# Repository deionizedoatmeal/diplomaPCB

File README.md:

### Bill of Materials:
Parts for the board:
| Part           | Quantity | Package          | Value          | Link                      |
| -------------- |:--------:|:----------------:|:--------------:|:-------------------------:|
| Microprocessor | 1        | QFN-56           | RP2040         |                           |
| 8MB SPI Flash  | 1        | SOIC-8           |                |                           |
| NeoPixel LED   | 37       | 1515 LED         | SK6805-E-J     | [Adafruit](https://www.adafruit.com/product/4492) |
| 7 Segement LED | 4        | LTS6760          | Common Cathode |                           | 
| Button Switch  | 5        | KMR2             | Momentary      |                           |
| Schottky Diode | 4        | SOD-123          | MBR0540        |                           |
| Transistor     | 14       | SOT-23           |                |                           |
| Crystal        | 1        | 2.5mm X 2.0mm    | 12.000 MHz     |                           |
| I2C Quad ADC   | 8        | SOIC-16          | PCF8591        |                           |
| Quad Logic Shifter | 1    | SOIC-16          | 74AHCT125      |                           |
| Voltage Regulator | 4     | SOT-23-5         | AP2112K-3.3    |                           |
| USB-C Receptacle | 5      | SMD              |                |                           |
| USB-C Plug     | 4        | SMD Edge Launch  | | [Adafruit](https://www.adafruit.com/product/4932) [Digikey](https://www.digikey.com/en/products/detail/adafruit-industries-llc/4932/13997774) |
| Resistor       | 23       | 0603/1608 Metric | 300 Ω          |                           |
| Resistor       | 10       | 0603/1608 Metric | 1 kΩ           |                           |
| Resistor       | 2        | 0603/1608 Metric | 5.11 kΩ        |                           |
| Resistor       | 60       | 0603/1608 Metric | 10 kΩ          |                           |
| Resistor       | 9        | 0603/1608 Metric | 1 MΩ           |                           |
| Resistor       | 2        | 0402/1005 Metric | 27 Ω           |                           |
| Capacitor      | 45       | 0805/2012 Metric | 0.1 µF         |                           |
| Capacitor      | 20       | 0085/2012 Metric | 10 µF          |                           |
| Capacitor      | 2        | 0402/1005 Metric | 27 pF          |                           |
| Capacitor      | 10       | 0402/1005 Metric | 100 nF         |                           |
| Capacitor      | 2        | 0402/1005 Metric | 1 µF           |                           |
| Magnets        | 112      | 3mm diameter x 1mm | Neodymium    |                           |

Parts for the game pieces (assuming 20 pieces for each nationality):
| Part           | Quantity | Package          | Value          | Link                      |
| -------------- |:--------:|:----------------:|:--------------:|:-------------------------:|
| Resistor       | 20       | Through Hole     | 60 kΩ          |                           |
| Resistor       | 20       | Through Hole     | 25 kΩ          |                           |
| Resistor       | 20       | Through Hole     | 13.4 kΩ        |                           |
| Resistor       | 20       | Through Hole     | 7.5 kΩ         |                           |
| Resistor       | 20       | Through Hole     | 4 kΩ           |                           |
| Resistor       | 20       | Through Hole     | 1.7 kΩ         |                           |
| Resistor       | 20       | Through Hole     | 0 Ω            |                           |
| Magnets        | 140      | 3mm diameter x 1mm | Neodymium    |                           |
| Pogo Pins      | 140      | anything that makes good contact with 2mm diameter pads and fits inside the piece | | [Digikey](https://www.digikey.com/en/products/detail/mill-max-manufacturing-corp/0965-0-15-20-80-14-11-0/2784013) |

### 3D Printing Pieces:

### Assembly Instructions:

### Software Install Instructions:
1) Hold down boot button on underside while plugging USB into computer.
2) When the `RPI-RP2` device shows up, copy [Adafruit's CircuitPython library](https://circuitpython.org/board/adafruit_feather_rp2040/) to the volume. 
3) Wait for the device to disappear and reappear as `CURCUITPY`, then copy all the libraries into the `lib` directory on the RP2040.
4) Finally, copy `code.py` into the `CURCUITPY` volume.

### Images

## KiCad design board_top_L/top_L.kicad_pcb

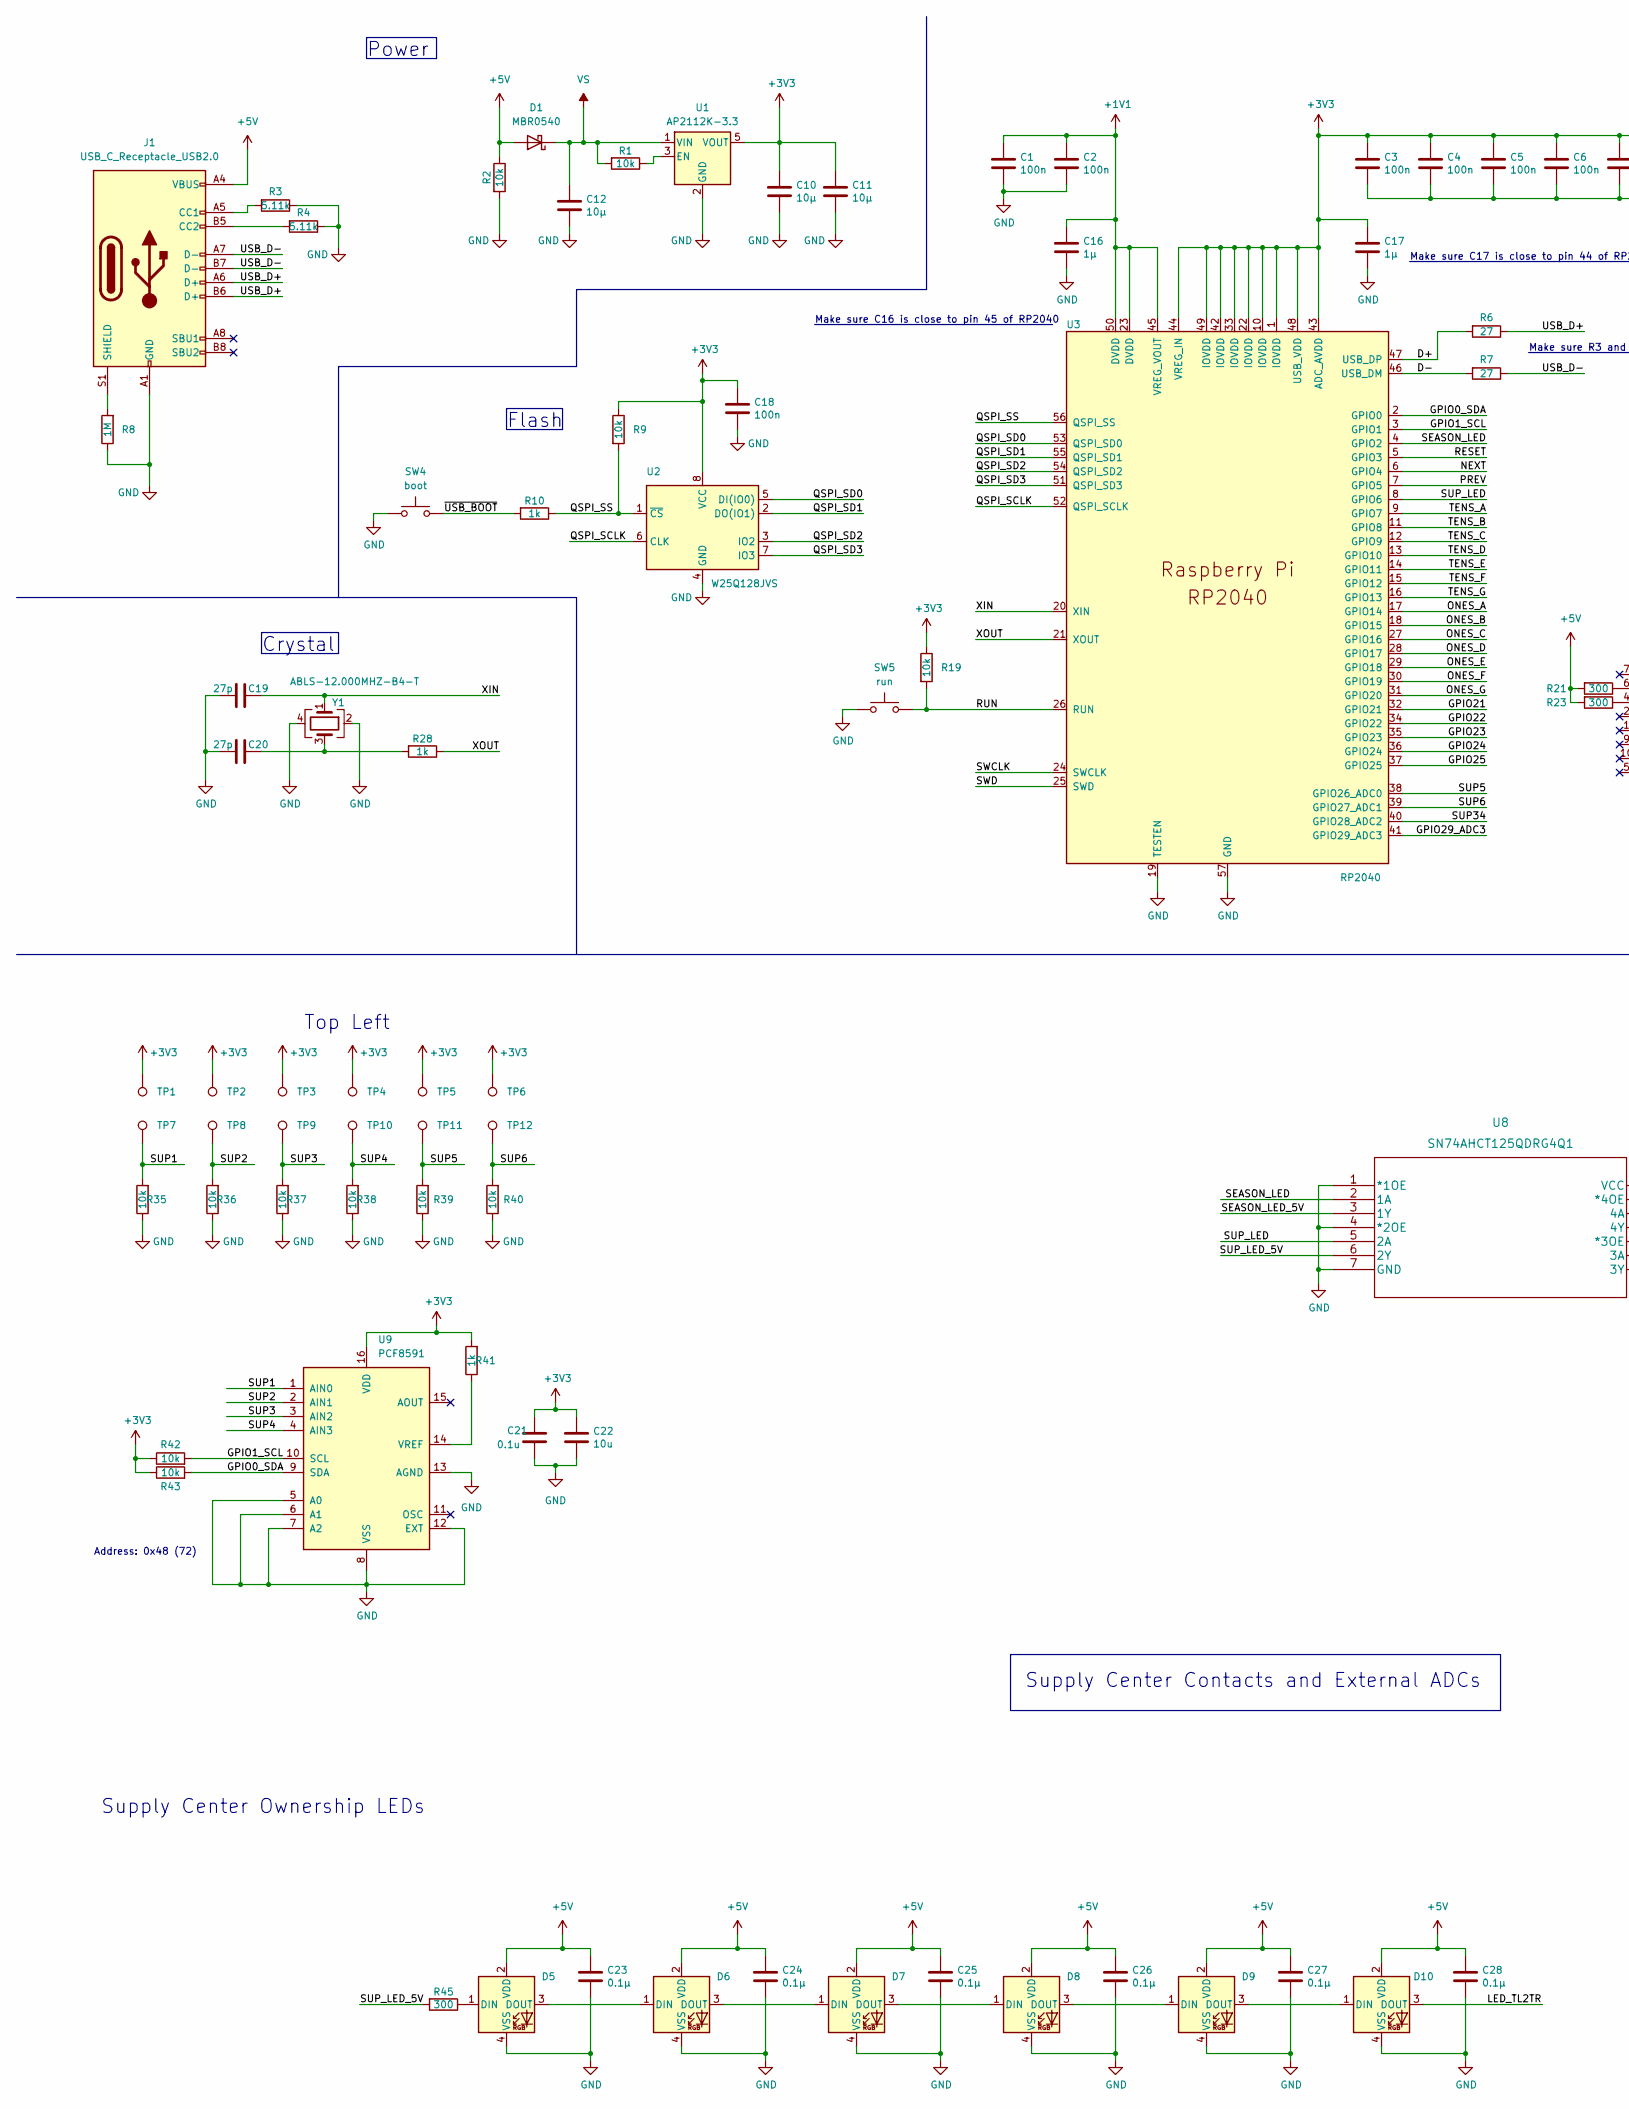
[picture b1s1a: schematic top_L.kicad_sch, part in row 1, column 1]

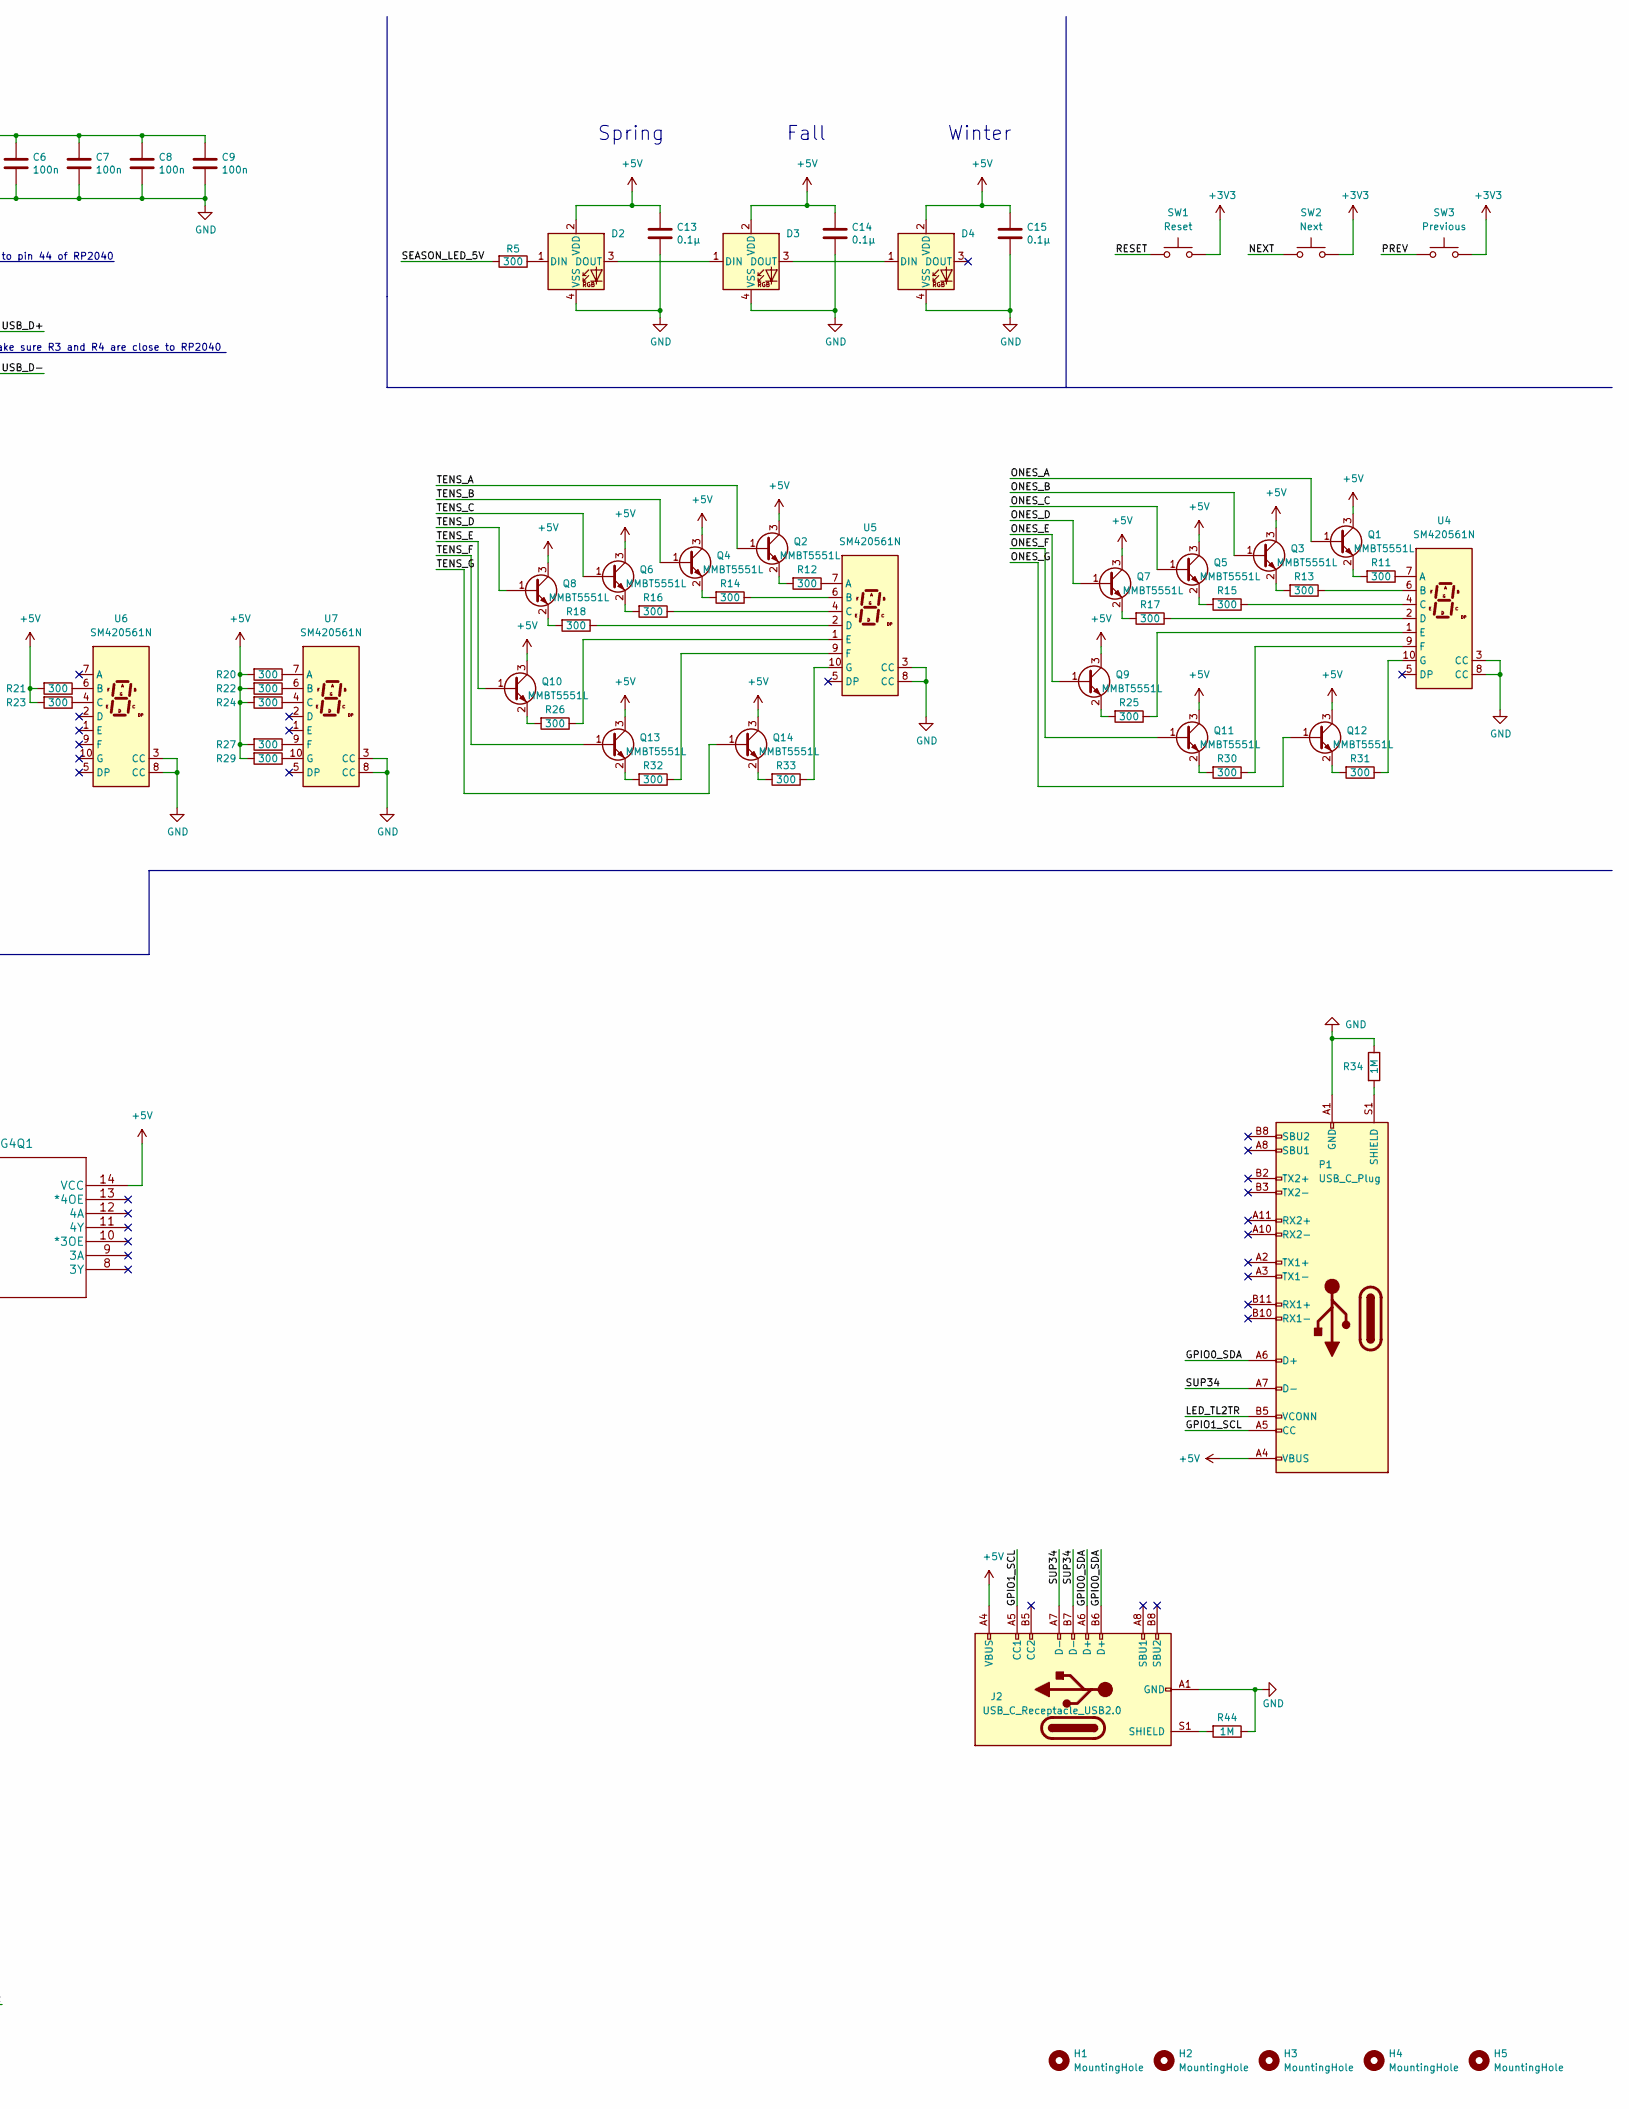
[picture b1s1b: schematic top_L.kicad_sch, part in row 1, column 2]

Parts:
C1, C2, C3, C4, C5, C6, C7, C8, C9, C18: 100n; C_0402_1005Metric
C10, C11, C12: 10µ; C_0805_2012Metric
C13, C14, C15, C23, C24, C25, C26, C27, C28: 0.1µ; C_0805_2012Metric
C16, C17: 1µ; C_0402_1005Metric
C19, C20: 27p; C_0402_1005Metric
C21: 0.1u; C_0805_2012Metric
C22: 10u; C_0805_2012Metric
D1: MBR0540; D_SOD-123
D2, D3, D4, D5, D6, D7, D8, D9, D10: SK6805-EC
H1, H2, H3, H4, H5: MountingHole; MountingHole_2.2mm_M2
J1, J2: USB_C_Receptacle_USB2.0; USB_C_Receptacle_HRO_TYPE-C-31-M-12
P1: USB_C_Plug; USB_C_Plug_edge_launch
Q1, Q2, Q3, Q4, Q5, Q6, Q7, Q8, Q9, Q10, Q11, Q12, Q13, Q14: MMBT5551L; SOT-23
R1, R2, R9, R19, R35, R36, R37, R38, R39, R40, R42, R43: 10k; R_0603_1608Metric
R3, R4: 5.11k; R_0603_1608Metric
R5, R11, R12, R13, R14, R15, R16, R17, R18, R20, R21, R22, R23, R24, R25, R26, R27, R29, R30, R31, R32, R33, R45: 300; R_0603_1608Metric
R6, R7: 27; R_0402_1005Metric
R8, R34, R44: 1M; R_0603_1608Metric
R10, R28, R41: 1k; R_0603_1608Metric
SW1: Reset; SW_Push_1P1T_NO_CK_KMR2
SW2: Next; SW_Push_1P1T_NO_CK_KMR2
SW3: Previous; SW_Push_1P1T_NO_CK_KMR2
SW4: boot; SW_Push_1P1T_NO_CK_KMR2
SW5: run; SW_Push_1P1T_NO_CK_KMR2
TP1, TP2, TP3, TP4, TP5, TP6, TP7, TP8, TP9, TP10, TP11, TP12: TestPoint; TestPoint_Pad_D2.0mm
U1: AP2112K-3.3; SOT-23-5
U2: W25Q128JVS; SOIC-8_5.23x5.23mm_P1.27mm
U3: RP2040; RP2040-QFN-56
U4, U5, U6, U7: SM420561N; 7SegmentLED_LTS6760_LTS6780
U8: SN74AHCT125QDRG4Q1
U9: PCF8591; SOIC-16W_7.5x10.3mm_P1.27mm
Y1: ABLS-12.000MHZ-B4-T; Crystal_SMD_3225-4Pin_3.2x2.5mm

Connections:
+1V1: C1.1, C2.1, C16.1, U3.23 (DVDD), U3.45 (VREG_VOUT), U3.50 (DVDD)
+3V3: C3.1, C4.1, C5.1, C6.1, C7.1, C8.1, C9.1, C10.1, C11.1, C17.1, C18.1, C21.1, C22.1, R9.1, R19.1, R41.2, R42.1, R43.1, SW1.2, SW2.2, SW3.2, TP1.1, TP2.1, TP3.1, TP4.1, TP5.1, TP6.1, U1.5 (VOUT), U2.8 (VCC), U3.1 (IOVDD), U3.10 (IOVDD), U3.22 (IOVDD), U3.33 (IOVDD), U3.42 (IOVDD), U3.43 (ADC_AVDD), U3.44 (VREG_IN), U3.48 (USB_VDD), U3.49 (IOVDD), U9.16 (VDD)
+5V: C13.1, C14.1, C15.1, C23.1, C24.1, C25.1, C26.1, C27.1, C28.1, D1.2 (A), D2.2 (VDD), D3.2 (VDD), D4.2 (VDD), D5.2 (VDD), D6.2 (VDD), D7.2 (VDD), D8.2 (VDD), D9.2 (VDD), D10.2 (VDD), J1.A4 (VBUS), J1.A9 (VBUS), J1.B4 (VBUS), J1.B9 (VBUS), J2.A4 (VBUS), J2.A9 (VBUS), J2.B4 (VBUS), J2.B9 (VBUS), P1.A4 (VBUS), P1.A9 (VBUS), P1.B4 (VBUS), P1.B9 (VBUS), Q1.3 (C), Q2.3 (C), Q3.3 (C), Q4.3 (C), Q5.3 (C), Q6.3 (C), Q7.3 (C), Q8.3 (C), Q9.3 (C), Q10.3 (C), Q11.3 (C), Q12.3 (C), Q13.3 (C), Q14.3 (C), R2.1, R20.2, R21.2, R22.2, R23.2, R24.2, R27.2, R29.2, U8.14 (VCC)
/D+: R6.2, U3.47 (USB_DP)
/D-: R7.2, U3.46 (USB_DM)
/GPIO0_SDA: J2.A6 (D+), J2.B6 (D+), P1.A6 (D+), R43.2, U3.2 (GPIO0), U9.9 (SDA)
/GPIO1_SCL: J2.A5 (CC1), P1.A5 (CC), R42.2, U3.3 (GPIO1), U9.10 (SCL)
/GPIO21: U3.32 (GPIO21)
/GPIO22: U3.34 (GPIO22)
/GPIO23: U3.35 (GPIO23)
/GPIO24: U3.36 (GPIO24)
/GPIO25: U3.37 (GPIO25)
/GPIO29_ADC3: U3.41 (GPIO29_ADC3)
/LED_TL2TR: D10.3 (DOUT), P1.B5 (VCONN)
/NEXT: SW2.1, U3.6 (GPIO4)
/ONES_A: Q1.1 (B), U3.17 (GPIO14)
/ONES_B: Q3.1 (B), U3.18 (GPIO15)
/ONES_C: Q5.1 (B), U3.27 (GPIO16)
/ONES_D: Q7.1 (B), U3.28 (GPIO17)
/ONES_E: Q9.1 (B), U3.29 (GPIO18)
/ONES_F: Q11.1 (B), U3.30 (GPIO19)
/ONES_G: Q12.1 (B), U3.31 (GPIO20)
/PREV: SW3.1, U3.7 (GPIO5)
/QSPI_SCLK: U2.6 (CLK), U3.52 (QSPI_SCLK)
/QSPI_SD0: U2.5 (DI(IO0)), U3.53 (QSPI_SD0)
/QSPI_SD1: U2.2 (DO(IO1)), U3.55 (QSPI_SD1)
/QSPI_SD2: U2.3 (IO2), U3.54 (QSPI_SD2)
/QSPI_SD3: U2.7 (IO3), U3.51 (QSPI_SD3)
/QSPI_SS: R9.2, R10.1, U2.1 (~CS), U3.56 (QSPI_SS)
/RESET: SW1.1, U3.5 (GPIO3)
/RUN: R19.2, SW5.2, U3.26 (RUN)
/SEASON_LED: U3.4 (GPIO2), U8.2 (1A)
/SEASON_LED_5V: R5.2, U8.3 (1Y)
/SUP1: R35.2, TP7.1, U9.1 (AIN0)
/SUP2: R36.2, TP8.1, U9.2 (AIN1)
/SUP3: R37.2, TP9.1, U9.3 (AIN2)
/SUP4: R38.2, TP10.1, U9.4 (AIN3)
/SUP5: R39.2, TP11.1, U3.38 (GPIO26_ADC0)
/SUP6: R40.2, TP12.1, U3.39 (GPIO27_ADC1)
/SUP34: J2.A7 (D-), J2.B7 (D-), P1.A7 (D-), U3.40 (GPIO28_ADC2)
/SUP_LED: U3.8 (GPIO6), U8.5 (2A)
/SUP_LED_5V: R45.2, U8.6 (2Y)
/SWCLK: U3.24 (SWCLK)
/SWD: U3.25 (SWD)
/TENS_A: Q2.1 (B), U3.9 (GPIO7)
/TENS_B: Q4.1 (B), U3.11 (GPIO8)
/TENS_C: Q6.1 (B), U3.12 (GPIO9)
/TENS_D: Q8.1 (B), U3.13 (GPIO10)
/TENS_E: Q10.1 (B), U3.14 (GPIO11)
/TENS_F: Q13.1 (B), U3.15 (GPIO12)
/TENS_G: Q14.1 (B), U3.16 (GPIO13)
/USB_D+: J1.A6 (D+), J1.B6 (D+), R6.1
/USB_D-: J1.A7 (D-), J1.B7 (D-), R7.1
/XIN: C19.1, U3.20 (XIN), Y1.1
/XOUT: R28.1, U3.21 (XOUT)
/~USB_BOOT: R10.2, SW4.2
GND: C1.2, C2.2, C3.2, C4.2, C5.2, C6.2, C7.2, C8.2, C9.2, C10.2, C11.2, C12.2, C13.2, C14.2, C15.2, C16.2, C17.2, C18.2, C19.2, C20.2, C21.2, C22.2, C23.2, C24.2, C25.2, C26.2, C27.2, C28.2, D2.4 (VSS), D3.4 (VSS), D4.4 (VSS), D5.4 (VSS), D6.4 (VSS), D7.4 (VSS), D8.4 (VSS), D9.4 (VSS), D10.4 (VSS), J1.A1 (GND), J1.A12 (GND), J1.B1 (GND), J1.B12 (GND), J2.A1 (GND), J2.A12 (GND), J2.B1 (GND), J2.B12 (GND), P1.A1 (GND), P1.A12 (GND), P1.B1 (GND), P1.B12 (GND), R2.2, R3.1, R4.1, R8.1, R34.1, R35.1, R36.1, R37.1, R38.1, R39.1, R40.1, R44.1, SW4.1, SW5.1, U1.2 (GND), U2.4 (GND), U3.19 (TESTEN), U3.57 (GND), U4.3 (CC), U4.8 (CC), U5.3 (CC), U5.8 (CC), U6.3 (CC), U6.8 (CC), U7.3 (CC), U7.8 (CC), U8.1 (*1OE), U8.4 (*2OE), U8.7 (GND), U9.5 (A0), U9.6 (A1), U9.7 (A2), U9.8 (VSS), U9.12 (EXT), U9.13 (AGND), Y1.2, Y1.4
unnamed: C20.1, R28.2, Y1.3
unnamed: D2.1 (DIN), R5.1
unnamed: D2.3 (DOUT), D3.1 (DIN)
unnamed: D3.3 (DOUT), D4.1 (DIN)
unnamed: D5.1 (DIN), R45.1
unnamed: D5.3 (DOUT), D6.1 (DIN)
unnamed: D6.3 (DOUT), D7.1 (DIN)
unnamed: D7.3 (DOUT), D8.1 (DIN)
unnamed: D8.3 (DOUT), D9.1 (DIN)
unnamed: D9.3 (DOUT), D10.1 (DIN)
unnamed: J1.A5 (CC1), R3.2
unnamed: J1.B5 (CC2), R4.2
unnamed: J1.S1 (SHIELD), R8.2
unnamed: J2.S1 (SHIELD), R44.2
unnamed: P1.S1 (SHIELD), R34.2
unnamed: Q1.2 (E), R11.2
unnamed: Q2.2 (E), R12.2
unnamed: Q3.2 (E), R13.2
unnamed: Q4.2 (E), R14.2
unnamed: Q5.2 (E), R15.2
unnamed: Q6.2 (E), R16.2
unnamed: Q7.2 (E), R17.2
unnamed: Q8.2 (E), R18.2
unnamed: Q9.2 (E), R25.2
unnamed: Q10.2 (E), R26.2
unnamed: Q11.2 (E), R30.2
unnamed: Q12.2 (E), R31.2
unnamed: Q13.2 (E), R32.2
unnamed: Q14.2 (E), R33.2
unnamed: R1.1, U1.3 (EN)
unnamed: R11.1, U4.7 (A)
unnamed: R12.1, U5.7 (A)
unnamed: R13.1, U4.6 (B)
unnamed: R14.1, U5.6 (B)
unnamed: R15.1, U4.4 (C)
unnamed: R16.1, U5.4 (C)
unnamed: R17.1, U4.2 (D)
unnamed: R18.1, U5.2 (D)
unnamed: R20.1, U7.7 (A)
unnamed: R21.1, U6.6 (B)
unnamed: R22.1, U7.6 (B)
unnamed: R23.1, U6.4 (C)
unnamed: R24.1, U7.4 (C)
unnamed: R25.1, U4.1 (E)
unnamed: R26.1, U5.1 (E)
unnamed: R27.1, U7.9 (F)
unnamed: R29.1, U7.10 (G)
unnamed: R30.1, U4.9 (F)
unnamed: R31.1, U4.10 (G)
unnamed: R32.1, U5.9 (F)
unnamed: R33.1, U5.10 (G)
unnamed: R41.1, U9.14 (VREF)
VS: C12.1, D1.1 (K), R1.2, U1.1 (VIN)

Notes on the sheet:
Winter
Crystal
Make sure C16 is close to pin 45 of RP2040
Address: 0x48 (72)
Top Left
Make sure C17 is close to pin 44 of RP2040
Supply Center Contacts and External ADCs
Supply Center Ownership LEDs
Spring
Fall
Make sure R3 and R4 are close to RP2040
Power
Flash

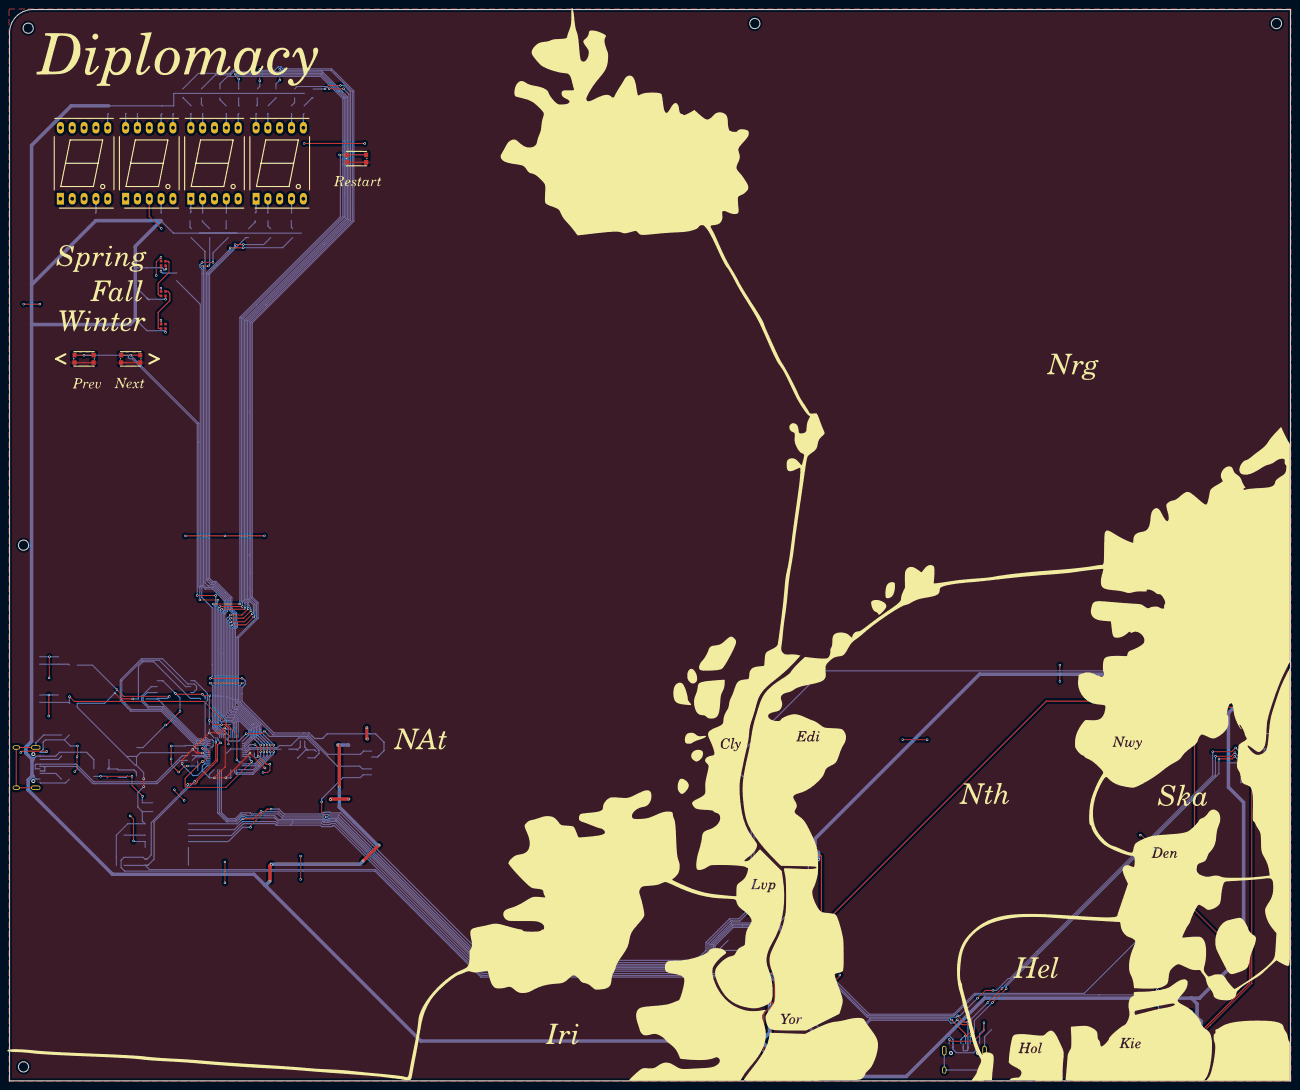
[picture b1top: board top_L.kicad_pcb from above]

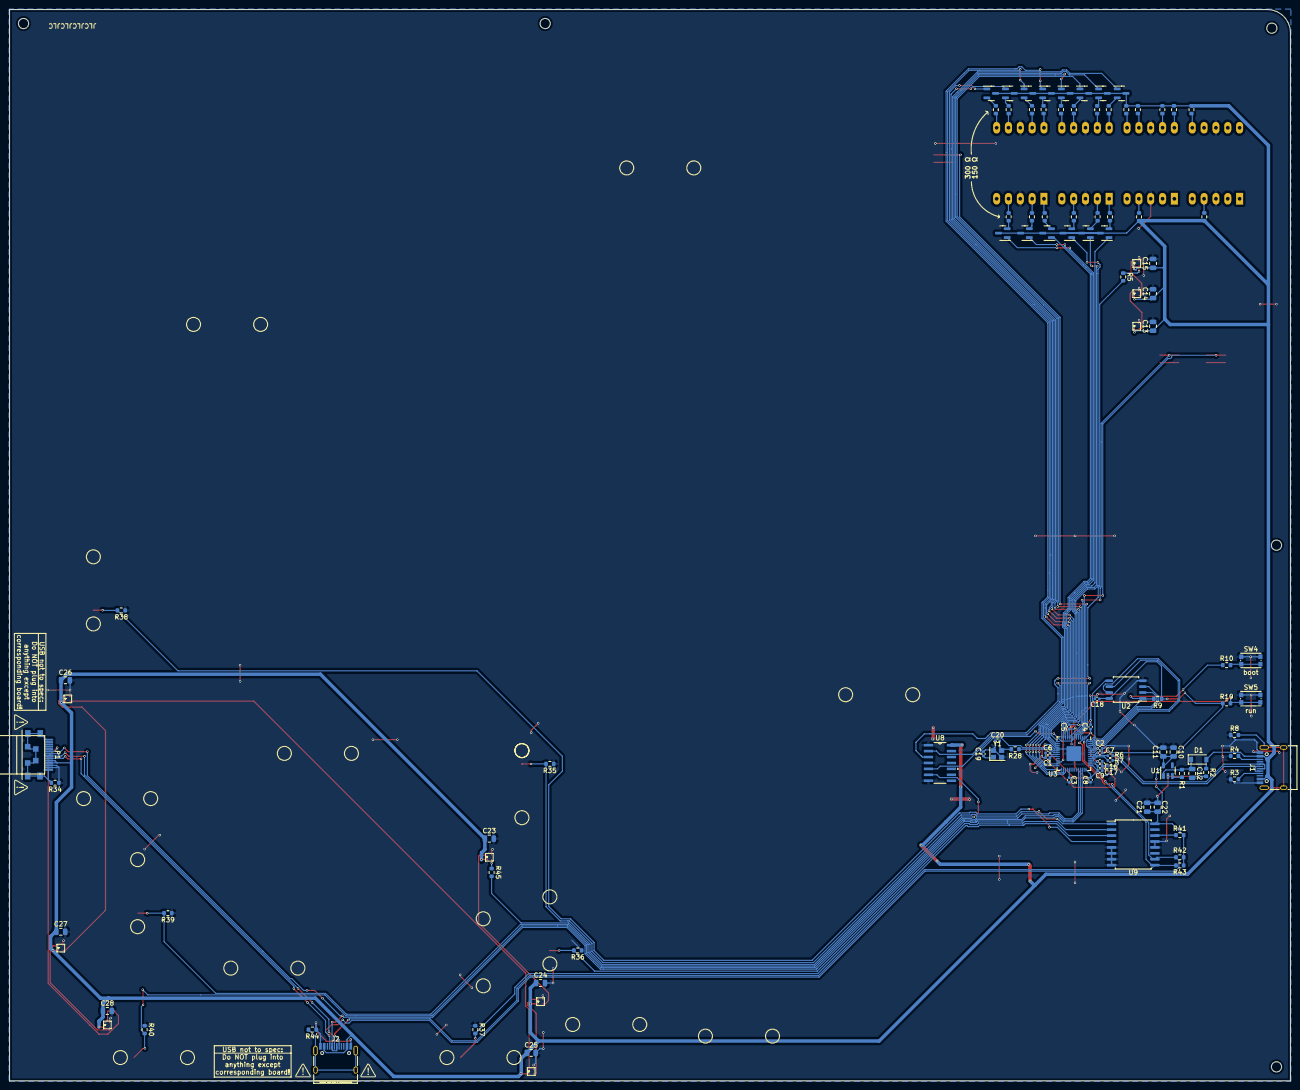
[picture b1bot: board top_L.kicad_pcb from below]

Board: 2 copper layers, 275.0 x 230.0 mm, 132 parts (99 on the bottom side), 102 nets.

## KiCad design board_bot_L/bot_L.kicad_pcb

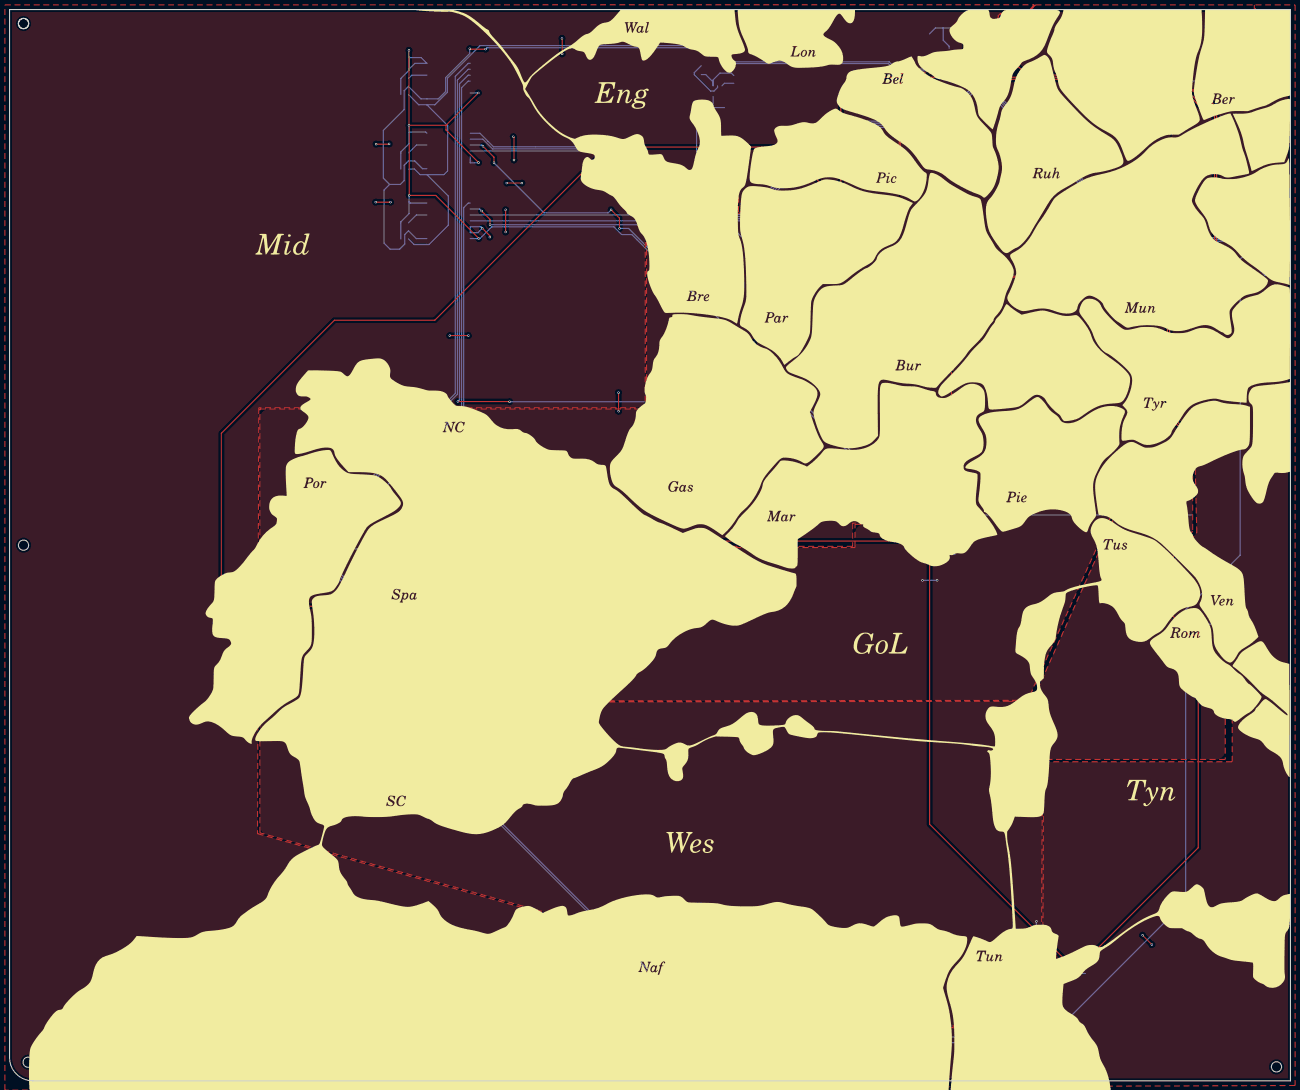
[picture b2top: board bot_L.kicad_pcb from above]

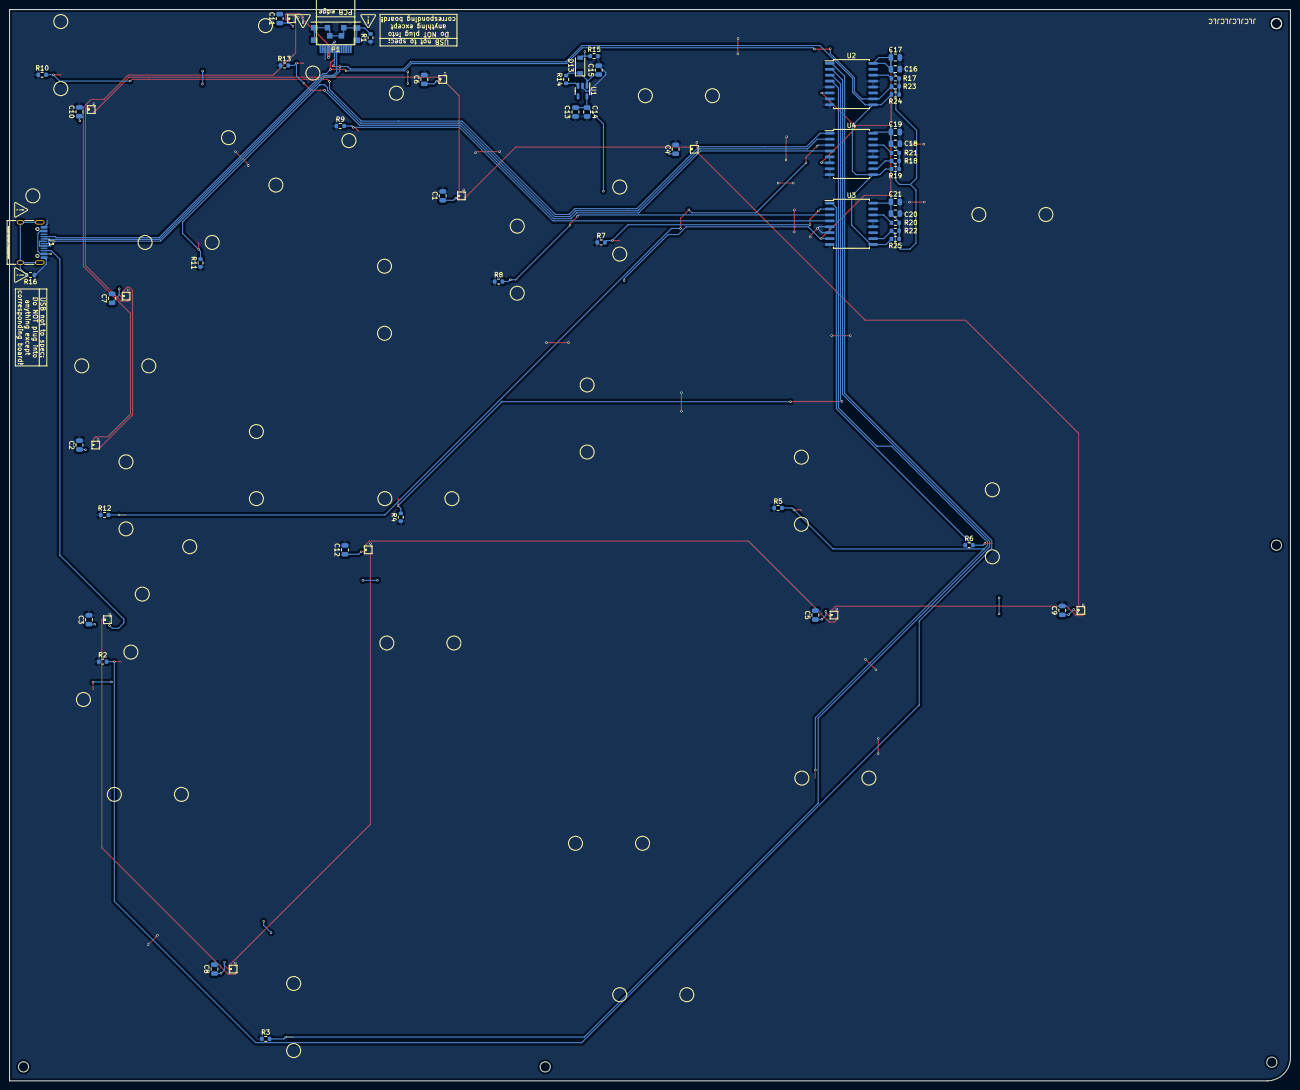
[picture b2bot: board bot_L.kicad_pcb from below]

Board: 2 copper layers, 275.0 x 230.0 mm, 96 parts (53 on the bottom side), 37 nets.

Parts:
C1, C2, C3, C4, C5, C6, C7, C8, C9, C10, C11, C12: 0.1µ; C_0805_2012Metric
C13, C14, C15: 10µ; C_0805_2012Metric
C16, C18, C20: 0.1u; C_0805_2012Metric
C17, C19, C21: 10u; C_0805_2012Metric
D1, D2, D3, D4, D5, D6, D7, D8, D9, D10, D11, D12: SK6805-EC
D13: MBR0540; D_SOD-123
H1, H2, H3, H4, H5: MountingHole; MountingHole_2.2mm_M2
J1: USB_C_Receptacle_USB2.0; USB_C_Receptacle_HRO_TYPE-C-31-M-12
P1: USB_C_Plug; USB_C_Plug_edge_launch
R1, R16: 1M; R_0603_1608Metric
R2, R3, R4, R5, R6, R7, R8, R9, R10, R11, R12, R13, R14, R15, R18, R19, R22, R23, R24, R25: 10k; R_0603_1608Metric
R17, R20, R21: 1k; R_0603_1608Metric
TP1, TP2, TP3, TP4, TP5, TP6, TP7, TP8, TP9, TP10, TP11, TP12, TP13, TP14, TP15, TP16, TP17, TP18, TP19, TP20, TP21, TP22, TP23, TP24, TP25, TP26: TestPoint; TestPoint_Pad_D2.0mm
U1: AP2112K-3.3; SOT-23-5
U2, U3, U4: PCF8591; SOIC-16W_7.5x10.3mm_P1.27mm

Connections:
+3V3: C13.1, C14.1, C16.1, C17.1, C18.1, C19.1, C20.1, C21.1, R17.2, R18.1, R19.1, R20.2, R21.2, R22.1, R23.1, R24.1, R25.1, TP1.1, TP2.1, TP3.1, TP4.1, TP5.1, TP6.1, TP7.1, TP8.1, TP9.1, TP10.1, TP11.1, TP12.1, TP25.1, U1.5 (VOUT), U2.6 (A1), U2.16 (VDD), U3.7 (A2), U3.16 (VDD), U4.5 (A0), U4.6 (A1), U4.16 (VDD)
+5V: C1.1, C2.1, C3.1, C4.1, C5.1, C6.1, C7.1, C8.1, C9.1, C10.1, C11.1, C12.1, D1.2 (VDD), D2.2 (VDD), D3.2 (VDD), D4.2 (VDD), D5.2 (VDD), D6.2 (VDD), D7.2 (VDD), D8.2 (VDD), D9.2 (VDD), D10.2 (VDD), D11.2 (VDD), D12.2 (VDD), D13.2 (A), J1.A4 (VBUS), J1.A9 (VBUS), J1.B4 (VBUS), J1.B9 (VBUS), P1.A4 (VBUS), P1.B9 (VBUS), R15.1
/GPIO0_SDA: J1.A6 (D+), J1.B6 (D+), P1.A6 (D+), R19.2, R24.2, R25.2, U2.9 (SDA), U3.9 (SDA), U4.9 (SDA)
/GPIO1_SCL: J1.A5 (CC1), P1.A5 (CC), R18.2, R22.2, R23.2, U2.10 (SCL), U3.10 (SCL), U4.10 (SCL)
/LED_BR2BL: D1.1 (DIN), J1.B5 (CC2)
/SUP10: R2.2, TP13.1, U2.1 (AIN0)
/SUP11: R3.2, TP14.1, U2.2 (AIN1)
/SUP12: R4.2, TP15.1, U2.3 (AIN2)
/SUP13: R5.2, TP16.1, TP26.1, U2.4 (AIN3)
/SUP14: R6.2, TP17.1, U3.1 (AIN0)
/SUP15: R7.2, TP18.1, U3.2 (AIN1)
/SUP16: R8.2, TP19.1, U3.3 (AIN2)
/SUP17: R9.2, TP20.1, U3.4 (AIN3)
/SUP18: R10.2, TP21.1, U4.1 (AIN0)
/SUP19: R11.2, TP22.1, U4.2 (AIN1)
/SUP20: R12.2, TP23.1, U4.3 (AIN2)
/SUP21: R13.2, TP24.1, U4.4 (AIN3)
/SUP34: J1.A7 (D-), J1.B7 (D-), P1.A7 (D-)
GND: C1.2, C2.2, C3.2, C4.2, C5.2, C6.2, C7.2, C8.2, C9.2, C10.2, C11.2, C12.2, C13.2, C14.2, C15.2, C16.2, C17.2, C18.2, C19.2, C20.2, C21.2, D1.4 (VSS), D2.4 (VSS), D3.4 (VSS), D4.4 (VSS), D5.4 (VSS), D6.4 (VSS), D7.4 (VSS), D8.4 (VSS), D9.4 (VSS), D10.4 (VSS), D11.4 (VSS), D12.4 (VSS), J1.A1 (GND), J1.A12 (GND), J1.B1 (GND), J1.B12 (GND), P1.A1 (GND), P1.B12 (GND), R1.1, R2.1, R3.1, R4.1, R5.1, R6.1, R7.1, R8.1, R9.1, R10.1, R11.1, R12.1, R13.1, R15.2, R16.1, U1.2 (GND), U2.5 (A0), U2.7 (A2), U2.8 (VSS), U2.12 (EXT), U2.13 (AGND), U3.5 (A0), U3.6 (A1), U3.8 (VSS), U3.12 (EXT), U3.13 (AGND), U4.7 (A2), U4.8 (VSS), U4.12 (EXT), U4.13 (AGND)
unnamed: D1.3 (DOUT), D2.1 (DIN)
unnamed: D2.3 (DOUT), D3.1 (DIN)
unnamed: D3.3 (DOUT), D4.1 (DIN)
unnamed: D4.3 (DOUT), D5.1 (DIN)
unnamed: D5.3 (DOUT), D6.1 (DIN)
unnamed: D6.3 (DOUT), D7.1 (DIN)
unnamed: D7.3 (DOUT), D8.1 (DIN)
unnamed: D8.3 (DOUT), D9.1 (DIN)
unnamed: D9.3 (DOUT), D10.1 (DIN)
unnamed: D10.3 (DOUT), D11.1 (DIN)
unnamed: D11.3 (DOUT), D12.1 (DIN)
unnamed: J1.S1 (SHIELD), R16.2
unnamed: P1.S1 (SHIELD), R1.2
unnamed: R14.1, U1.3 (EN)
unnamed: R17.1, U2.14 (VREF)
unnamed: R20.1, U3.14 (VREF)
unnamed: R21.1, U4.14 (VREF)
VS: C15.1, D13.1 (K), R14.2, U1.1 (VIN)
